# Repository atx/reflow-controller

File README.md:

reflow-controller
=================

Reflow Oven Controller

To build the firmware you have to do the following:

```
$ git submodule update --init
$ cd thirdparty/ChibiOS-RT/ext
$ tar -xvf uip-1.0.tar.gz
$ unzip uip-1.0.patches.zip
$ cd ../../src
$ make
```

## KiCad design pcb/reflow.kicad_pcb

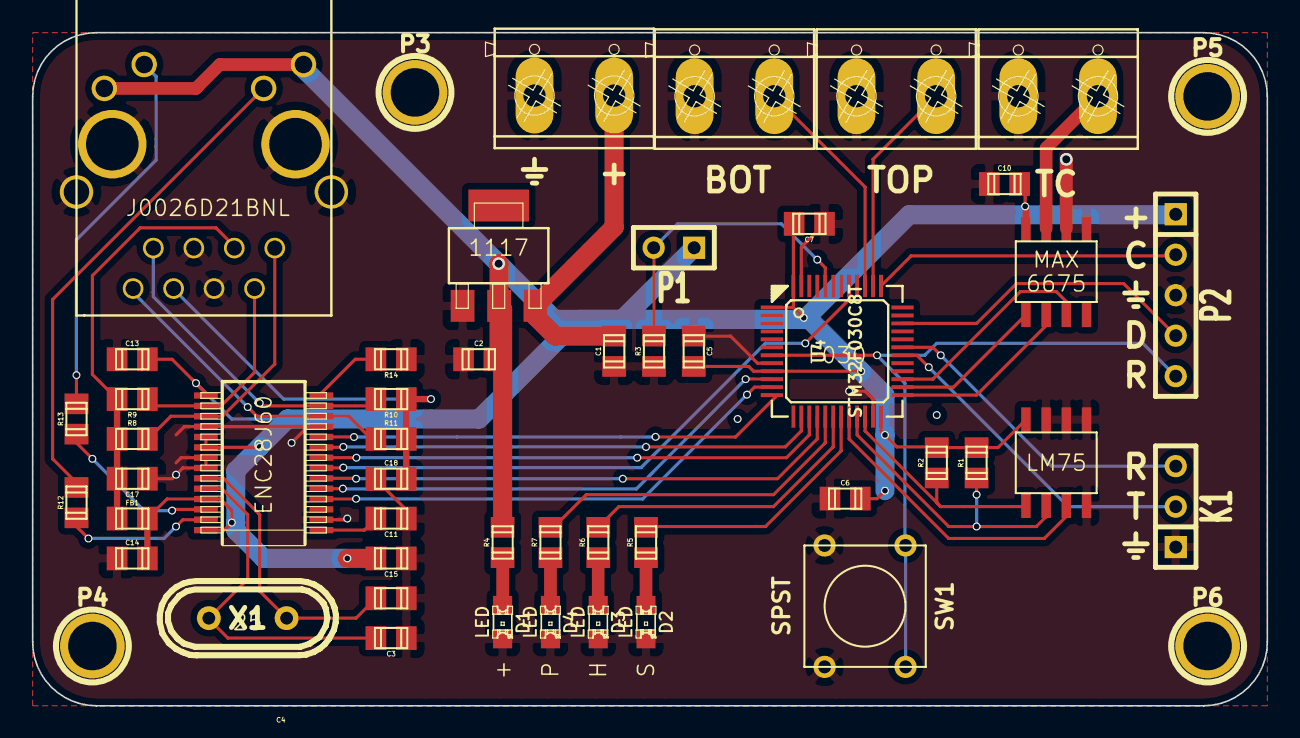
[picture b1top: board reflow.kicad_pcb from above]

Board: 2 copper layers, 77.5 x 42.2 mm, 52 parts (0 on the bottom side), 46 nets.

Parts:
C1: 1uF; c_0805
C2, C11: 10uF; c_0805
C3, C4: 22pF; c_0805
C5: 4.7uF; c_0805
C6, C7, C10, C13, C14, C15, C17, C18: 100nF; c_0805
D1, D2, D3, D4: LED; LED-0805
FB1: FERRITE_BEAD; c_0805
H1: J0026D21BNL
J1: TC-K; dp_devices-TERMINAL_BLOCK_2P_5
J2: RELAY-TOP; dp_devices-TERMINAL_BLOCK_2P_5
J3: RELAY-BOT; dp_devices-TERMINAL_BLOCK_2P_5
J4: PWR; dp_devices-TERMINAL_BLOCK_2P_5
K1: CONN_3; SIL-3
P1: CONN_2; SIL-2
P2: CONN_5; SIL-5
P3, P4, P5, P6: CONN_1; 1pin
R1, R2: 1k8; c_0805
R3: 10k; c_0805
R4, R5, R6, R7: R; c_0805
R8, R9, R10, R11: 49.9 1%; c_0805
R12, R13: 120; c_0805
R14: 2k32; c_0805
SW1: SPST; SW_PUSH_SMALL
U1: MAX6675; dp_devices-SO-8
U2: ENC28J60-SSOP; microchip-enc28j60-SSOP28
U3: REG1117; burr-brown-3-SOT223
U4: STM32F030C8T; lqfp-48
U5: LM75; dp_devices-SO-8
X1: 25MHz; Crystal_HC49-U_Vertical

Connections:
+3.3V: C2.1, C5.1, C6.1, C7.1, C10.1, C13.1, C14.1, C15.1, FB1.1, H1.9, H1.12, P1.1, P2.1, R1.1, R2.1, R4.1, U1.4, U2.15, U2.19, U2.20, U2.25, U2.28, U3.2, U4.1, U4.9, U4.24, U4.48, U5.8
+5V: C1.1, J4.1, U3.3
BOOT0: P1.2, R3.1, U4.44
E-CS: U2.9, U4.14
E-INT: U2.4, U4.11
E-RST: U2.10, U4.12
E-SCK: U2.8, U4.15
E-SI: U2.7, U4.41
E-SO: U2.6, U4.16
E-WOL: U2.5, U4.10
GND: C1.2, C2.2, C3.2, C4.2, C5.2, C6.2, C7.2, C10.2, C11.2, C13.2, C14.2, C15.2, C17.2, C18.2, D1.2, D2.2, D3.2, D4.2, H1.4, H1.5, J1.2, J2.2, J3.2, J4.2, K1.1, P2.3, R3.2, R14.2, SW1.2, U1.1, U1.2, U2.2, U2.11, U2.18, U2.21, U2.22, U3.1, U4.8, U4.23, U4.47, U5.4, U5.5, U5.6, U5.7
I2C_SCL: R1.2, U4.21, U5.2
I2C_SDA: R2.2, U4.22, U5.1
LED-HEAT: R6.1, U4.18
LED-PRG: R7.1, U4.17
LED-SYS: R5.1, U4.19
M-NRST: P2.5, SW1.1, U4.7
unnamed: C3.1, U2.24, X1.1
unnamed: C4.1, U2.23, X1.2
unnamed: C11.1, U2.1
unnamed: C17.1, FB1.2, H1.3, R8.2, R9.1
unnamed: C18.1, H1.6, R10.2, R11.1
unnamed: D1.1, R4.2
unnamed: D2.1, R5.2
unnamed: D3.1, R6.2
unnamed: D4.1, R7.2
unnamed: H1.1, R8.1, U2.17
unnamed: H1.2, R9.2, U2.16
unnamed: H1.7, R10.1, U2.13
unnamed: H1.8, R11.2, U2.12
unnamed: H1.10, R12.1
unnamed: H1.11, R13.1
unnamed: J1.1, U1.3
unnamed: R12.2, U2.27
unnamed: R13.2, U2.26
unnamed: R14.1, U2.14
OVERTEMP: U4.20, U5.3
RELAY-BOT: J3.1, U4.39
RELAY-TOP: J2.1, U4.38
RX: K1.3, U4.31
SWCLK: P2.2, U4.37
SWDIO: P2.4, U4.34
T-CS: U1.6, U4.25
T-SCK: U1.5, U4.26
T-SO: U1.7, U4.27
TX: K1.2, U4.30

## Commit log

2014-09-21 thirdparty: Add ChbioOS and kicad-library
2014-09-21 pcb: Add the KiCAD files
2014-10-28 src: Initial source commit
2014-10-28 pcb: Add .svg renders
    Add .svg renders of the board and the schematic.
2014-10-28 : Add the LICENSE file
    Add the LICENSE file containing GPLv3
2014-10-28 : Add README.md
